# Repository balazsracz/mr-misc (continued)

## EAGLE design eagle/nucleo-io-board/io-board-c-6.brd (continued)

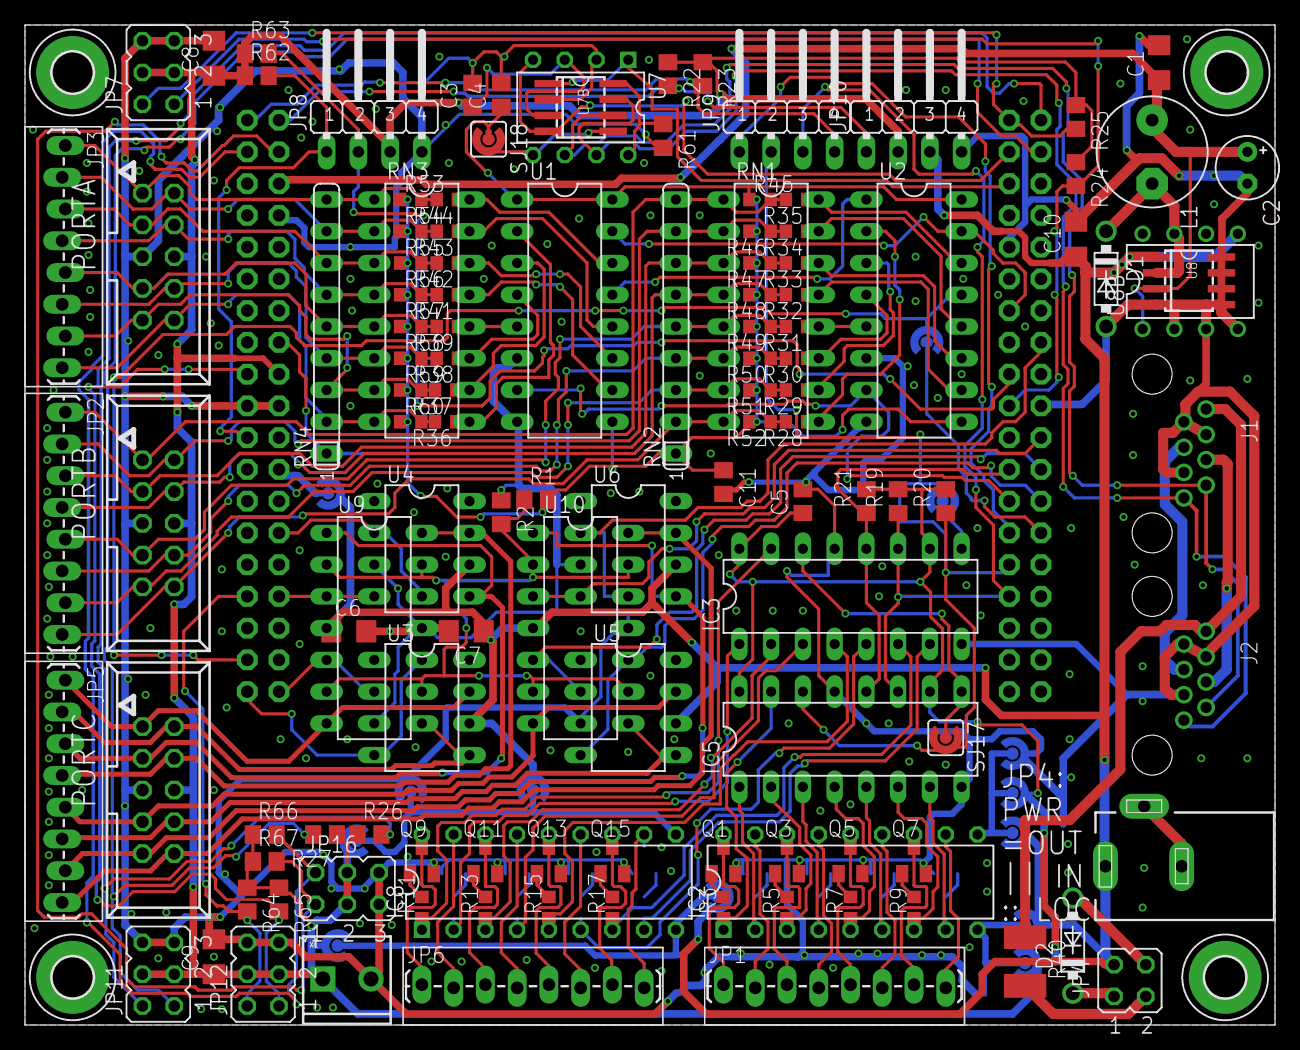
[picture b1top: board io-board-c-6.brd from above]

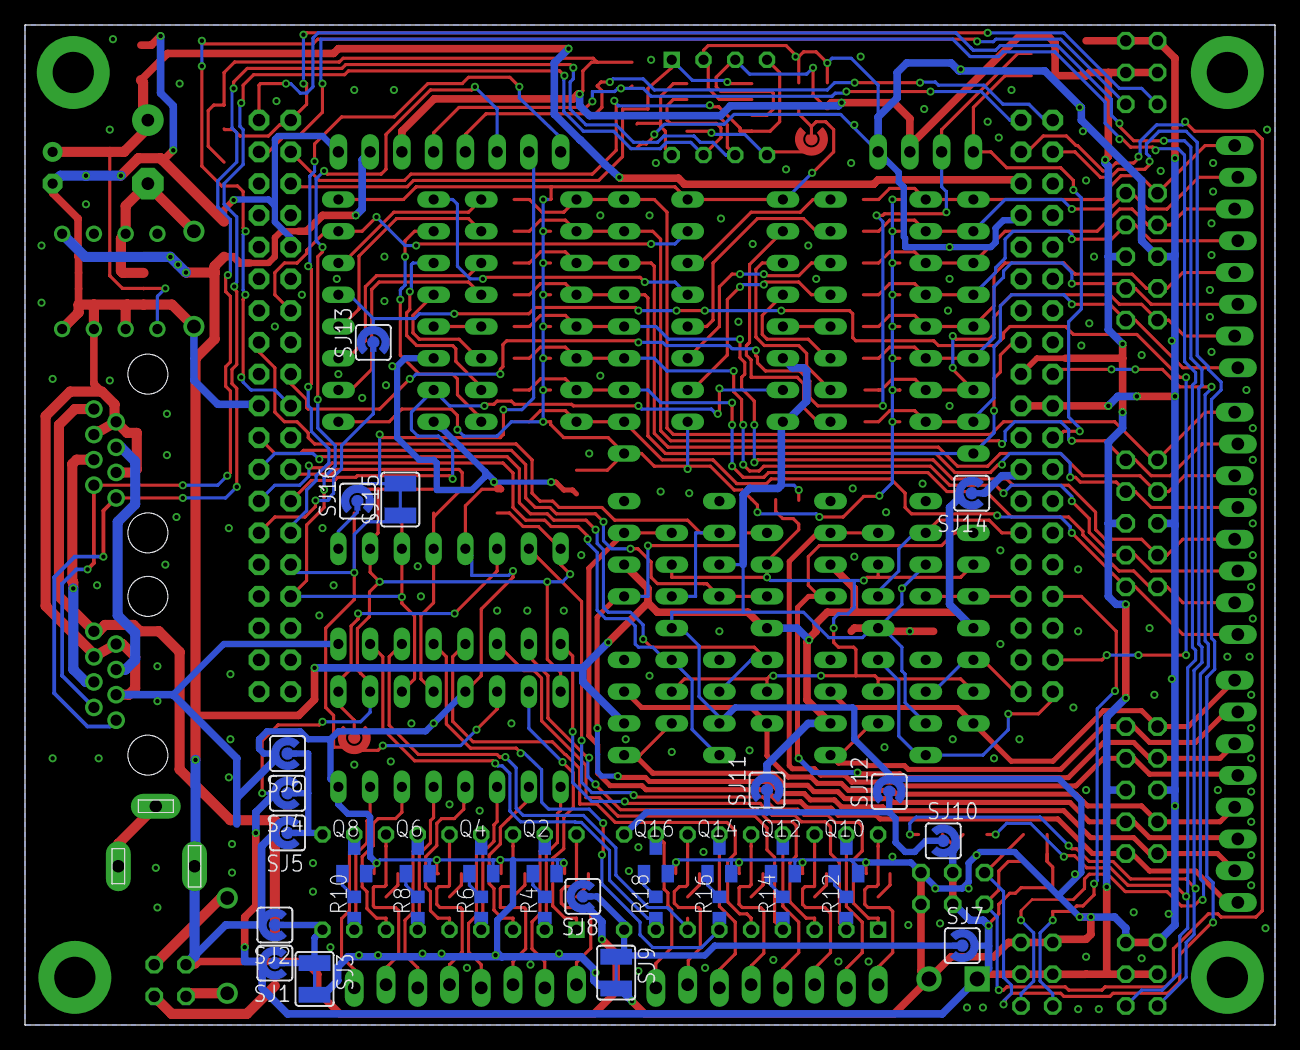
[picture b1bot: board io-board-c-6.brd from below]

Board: 2 copper layers, 100.0 x 80.0 mm, 161 parts (32 on the bottom side), 144 nets.
